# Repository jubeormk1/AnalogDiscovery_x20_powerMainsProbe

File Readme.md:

# ADVISE: This project is a work in progress

This is the first version of the instruments. Please review and make constructive comments about the design. Use under your own risk for evaluation purposes only. After my internal validation the an "Stable version will be release." After I get this right more board to improve the versatility of the great [AnalogDiscovery board by Agilent](https://analogdiscovery.com/) will be release.

# Introduction

This is a design initially created to look a the shape of mains outlets. I design it to check the total harmonic distortion of a generator outlet with a x20 reduction.

It has two inlets to measure two active line with the same neutral, i.e. the signal before and after a power line filter. It is intended to measure only voltage up to a frequency of at least 100kHz without a significant reduction of the signal (under 3db).

The connector is made to be connected to an Analog Discovery Digilent Instrument. It has been design to compensate the internal impedance of this particular instrument (1MOhm, 24pF). If you have one of these you can tune it so it works at it's best.

So far the version v0.1 has been release with some issues. This issues are related with the PCB layout, mainly related to the main connector pins and an unconnected pin. Apart from that the measured frequency response tested with flying wires is a success as you can see in the next frequency response analysis.

The frequential response is almost flat with a small deviation only 0.39dB at 100kHz. The phase shift is kept close to zero for the whole analysis from 10Hz to 400kHz with an increasing positive slope from 400kHz ending under 5 degrees.

# Warnings

* This circuit is intended to be use to measure monophasic power mains up to 240Vrms. Such a voltage imply electric risk and only professionals with the right skills and safety protections should use it.

* The neutral of the power outlet under test will be connected to the GND of the instruments in use. Before any use make sure that there is no connection from the GND of the instrument with the protective heart (PE) of your installation.

* If the GND of your instrument is connected to PE you should isolate it using an appropiate method, which could be an isolation transformer.

* Prior to the first use it is necessary to adjust the gain of both channels using resistor trims. See the tune procedure section in this document to understand the procedure.

* If used without a plastic case, provide adequate means to prevent accidental contact with the AC voltage present by isolating the exposed metal points.

* If unsure about above conditions are met please don't use this design.

* Use under your responsibility

* Any damage caused by the use of this design is responsibility of the licensed professional using it

# Specifications

After tuned this circuit delivered:
* Two channels connected to scope 1 and 2
* An x20 attenuation in both channels
* AC/DC coupling mode via jumpers selection in each channels
* Impedance matching to obtain an  uniform amplitude and phase frequency response from DC to at least 100kHz
* Protection for over voltage (varistor) rated to the used device

# Tune procedure

This procedure consist in two tunning procedures and a measurement of the frequency response. The order is important in this procedure. Once tunned at the circuit best. The tunning procedure is made with very low voltages (5V). This is done to prevent any damage to the board or the instrument used. If unexpected volts appear please check the components values before continuing and correct any anomaly. A visual inspection of the board is also recommended to look for short circuits, missing components or bad soldering points.

## Required equipment:
* Personal Computer
* Digilent Analog Discovery (R) Instrument
* Software Digilent Waveforms(R)
* Small isolated flat screwdriver
* Male to male connection leads
* Recommended but not required: multimeter

## Tunning the gain of a channel

Repeat this procedure for channel one and channel two.

1. Connect the jumpers of the channel under test in DC position.
2. Connect a male to male lead from GEN1 to the  in the appropriated input connector with a the pin socket corresponding to the channel under test
3. Connect the extension board to an Analog Discovery Digilent Instrument
4. Using Waveforms>Wavegen generate a DC signal in generator 1 channel of 5 Volts
5. Using Waveforms>Scope or Waveforms>Voltmeter obtain the value at the channel that you are calibrating.
6. Turn the dial on the trim resistor until you obtain 5/20 V (0.25V)

## Tunning the frequency response of a channel

Repeat this procedure for channel one and channel two. Use the channel not being tested as auxiliary channel.

1. Connect the jumpers of each channels in DC position.
2. Connect a male to male lead from GEN1 to the  in the appropriated input connector with a the pin socket corresponding to the channel under test
3. Connect a male to male lead from the channel you are not testing to GEN1
4. Connect the extension board to an Analog Discovery Digilent Instrument
5. Using Waveforms>Wavegen generate an square signal in generator 1 channel of +-5 Volts at a frequency of 10Hz
6. Using Waveforms>Scope obtain a good scope of the rising edge of the signal generated by the waveform generator and the reading in the channel you are adjusting
7. At this point you should have a signal with an amplitude of 1/20 from the channel under test to the auxiliary channel.
7. Turn the dial on the trim capacitor until you get the smaller possible raising time without overshooting.

## Measurement of the frequency response.

Repeat this procedure for channel one and channel two. Use the channel not being tested as auxiliary channel. Do this after you calibrate the gain and the frequency response. You can do it beforehand to check how wrong the probe was and compare it to an adjusted channel.

1. Connect the jumpers of each channels in DC position.
2. Connect a male to male lead from GEN1 to the  in the appropriated input connector with a the pin socket corresponding to the channel under test
3. Connect a male to male lead from the channel you are not testing to GEN1
4. Connect the extension board to an Analog Discovery Digilent Instrument

5. Using Digilent Waveforms>Network Analyser configure an acquisition from 10Hz to 10MHz and 300 samples

6. Initiate a single acquisition

7. Note down the frequency where the signal drop 3dBs from the 10Hz response. This is the bandwidth of your channel

8. Note down the phase at it's minimum and maximum values

9. Repeat the frequency response tunning until you get the best bandwidth

# License

Analog Discovery (R) and Waveforms(R) are Digilent trademarks.

The license is described in the file 'LICENSE'.

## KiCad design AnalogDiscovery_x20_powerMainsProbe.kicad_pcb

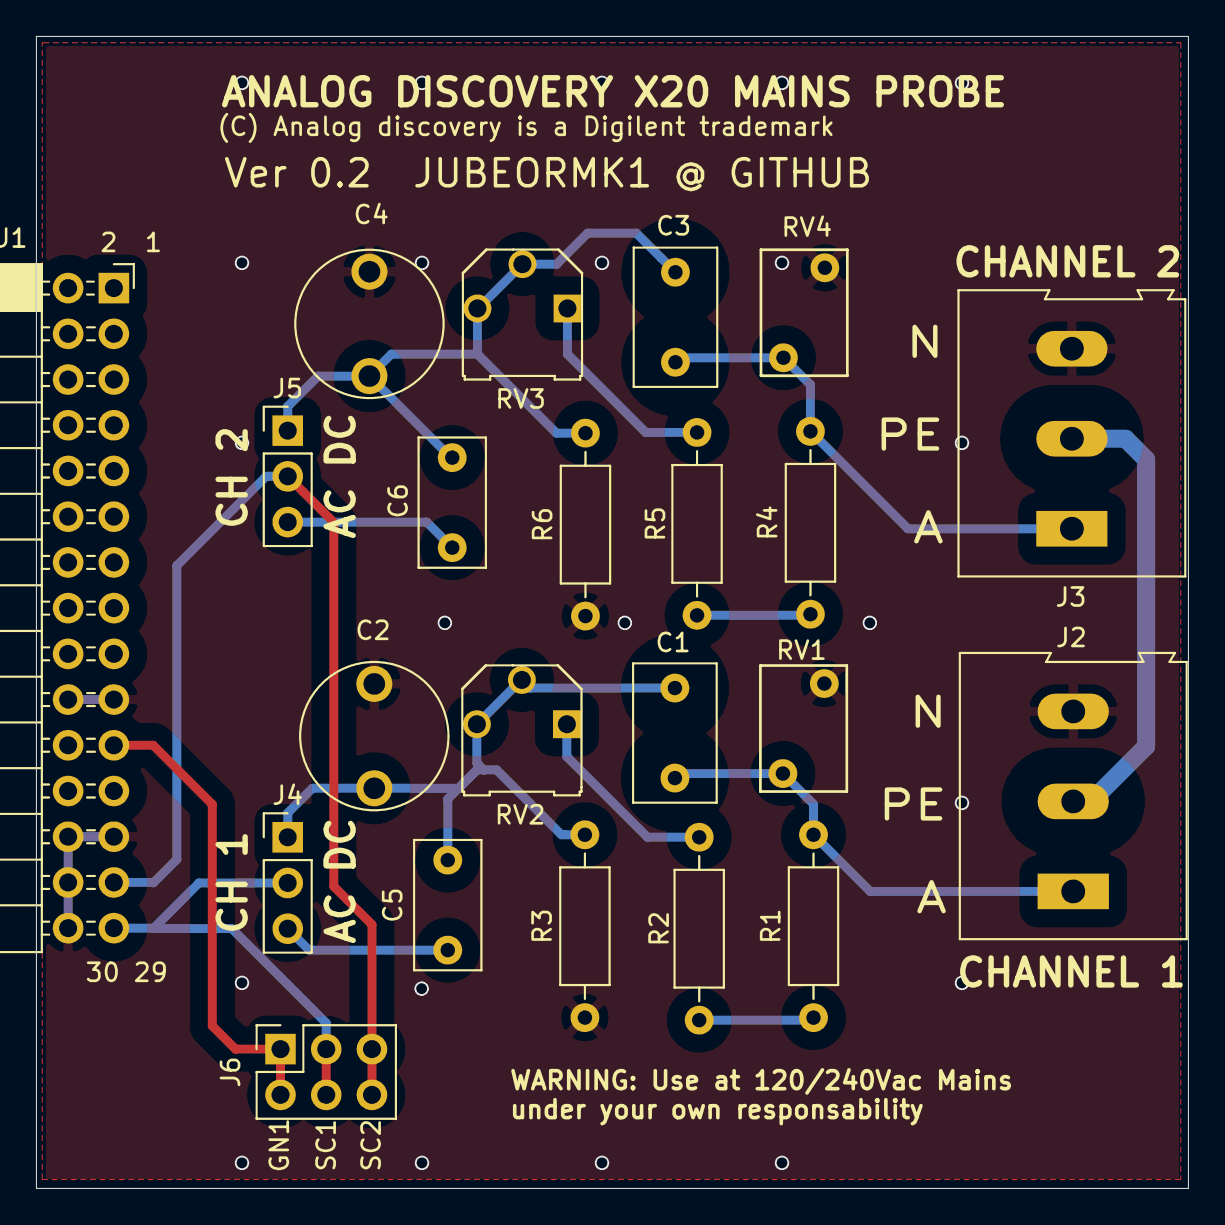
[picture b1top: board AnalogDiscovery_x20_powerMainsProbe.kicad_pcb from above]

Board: 2 copper layers, 64.0 x 64.0 mm, 22 parts (0 on the bottom side), 14 nets.

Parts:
C1, C3: 5p6; C_Disc_D7.5mm_W4.4mm_P5.00mm
C2, C4: 9-70p; C_trimmer_Axial_6.7mm
C5, C6: 0.1uF; C_Rect_L7.0mm_W3.5mm_P5.00mm
J1: Conn_02x15_Counter_Clockwise; PinSocket_2x15_P2.54mm_Horizontal
J2, J3: Conn_01x03_Female; TerminalBlock_Altech_AK300-3_P5.00mm
J4, J5: Conn_01x03_Male; PinHeader_1x03_P2.54mm_Vertical
J6: Conn_02x03_Counter_Clockwise; PinSocket_2x03_P2.54mm_Vertical
R1, R4: 9M1; R_Axial_DIN0207_L6.3mm_D2.5mm_P10.16mm_Horizontal
R2, R5: 220k; R_Axial_DIN0207_L6.3mm_D2.5mm_P10.16mm_Horizontal
R3, R6: 1M; R_Axial_DIN0207_L6.3mm_D2.5mm_P10.16mm_Horizontal
RV1, RV4: 270VAC Breakdown 720V; RV_Disc_D7mm_W4.8mm_P5mm
RV2, RV3: 500k; Potentiometer_Bourns_3306P-1-504

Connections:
/VIN_SC1_P: J1.29, J4.2, J6.3, J6.4
/VIN_SC2_P: J1.27, J5.2, J6.5, J6.6
/VOUT_AWG1: J1.21, J6.1, J6.2
GND: C2.2, C4.2, J1.19, J1.20, J1.25, J1.26, J1.28, J1.30, J2.3, J3.3, R3.1, R6.1, RV1.2, RV4.2
unnamed: C1.1, C2.1, C5.1, J4.1, R3.2, RV2.2, RV2.3
unnamed: C1.2, J2.1, R1.2, RV1.1
unnamed: C3.1, C4.1, C6.1, J5.1, R6.2, RV3.2, RV3.3
unnamed: C3.2, J3.1, R4.2, RV4.1
unnamed: C5.2, J4.3
unnamed: C6.2, J5.3
unnamed: R1.1, R2.2
unnamed: R2.1, RV2.1
unnamed: R4.1, R5.2
unnamed: R5.1, RV3.1

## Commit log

2019-10-08 First commit with the base design
    Including Readme, schematics, board, gerbers and drill files.
2019-10-08 modified the license section at Readme.md
2019-11-24 Assembled circuit for version 1.0
    This is the first pcb version. I am pretty sure that it is going to work fine since there is not much change from the previous prototypes. **There are two jumpers missing in the photo, they should go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
2019-11-24 Updated Readme.md
    - Advising that this project is still in a prerelease
    - Adding an image to the first PCB assembled
2019-11-24 test folder with graphical documentation added
2019-11-25 Updated Readme.md
    Added some information related to the test with the board v0.1 release.
    Fixed several typos. Shame on me!
2019-11-25 Solved issue #10
2019-11-25 Issue #3 fixed.
    J1 aligned with board edge
2019-11-25 Issue #9 fixed. The resistor pin separation has been change from 6 to 10mm
2019-11-25 issue #2 Hole size updated to 0.8mm
2019-11-25 Footprint fixed for potentiometers
